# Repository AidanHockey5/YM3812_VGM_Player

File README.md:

# YM3812_VGM_Player
A Video Game Music player based on the YM3812 (OPL2) and Teensy 3.5.

You can view this project in action here:
https://www.youtube.com/watch?v=aLaUDFnNqQc

# Information about the main sound chips and VGM

The YM3812, AKA OPL2 was a staple FM soundchip of the early 1990's. It claim to fame was its inclusion on the Adlib and Soundblaster soundcards. OPL2 is THE FM sound of 1990's PC gaming.

VGM stands for Video Game Music, and it is a 44.1KHz logging format that stores real soundchip register information. My player will parse these files and send the data to the appropriate chips. You can learn more about the VGM file format here: http://www.smspower.org/Music/VGMFileFormat

http://www.smspower.org/uploads/Music/vgmspec170.txt?sid=58da937e68300c059412b536d4db2ca0

# Hook-up Guide

Teensy 3.5 | YM
------------ | -------------
23, 22, 21...17, 16 | D0-D7
34  | CS
33 | RD
32 | WR
31 | A0
30 | IC
29 | IRQ

The YM3812 requires a 3.579545 MHz signal to function properly. I just used a full-can crystal for this, but any clock source of that speed will work.
You will also need a Y3014B DAC IC along with an OP-amp (LM358).

# SD Card Information
The Teensy 3.5 has a built-in, high speed micro-SD card reader. You must format your SD card to Fat32 in order for this device to work correctly. Your SD card must only contain uncompressed .vgm files. VGZ FILES WILL NOT WORK! You may download .vgz files and use [7zip](http://www.7-zip.org/download.html) to extract the uncompressed file out of them. Vgm files on the SD card do not need to have the .vgm extension. As long as they contain valid, uncompressed vgm data, they will be read by the program regardless of their name.
You can find VGM files by Googling "myGameName VGM," or by checking out sites like http://vgmrips.net/packs/

# Control Over Serial
You can use a serial connection to control playback features. The commands are as follows:

Command | Result
------------ | -------------
\+ | Next Track
\- | Previous Track
\* | Random Track
\/ | Toggle Shuffle Mode
\. | Toggle Song Looping
r: | Request song

A song request is formatted as follows: ```r:mySongFile.vgm```
Once a song request is sent through the serial console, an attempt will be made to open that song file. The file must exist on the Teensy's SD card, and spelling/capitalization must be correct.
Need an easy-to-use serial console? [I've made one here.](https://github.com/AidanHockey5/OpenArduinoSerialConsole)

# Schematic

[PDF](https://github.com/AidanHockey5/YM3812_VGM_Player/raw/master/Schematics/OPL2_VGM_Player.pdf)

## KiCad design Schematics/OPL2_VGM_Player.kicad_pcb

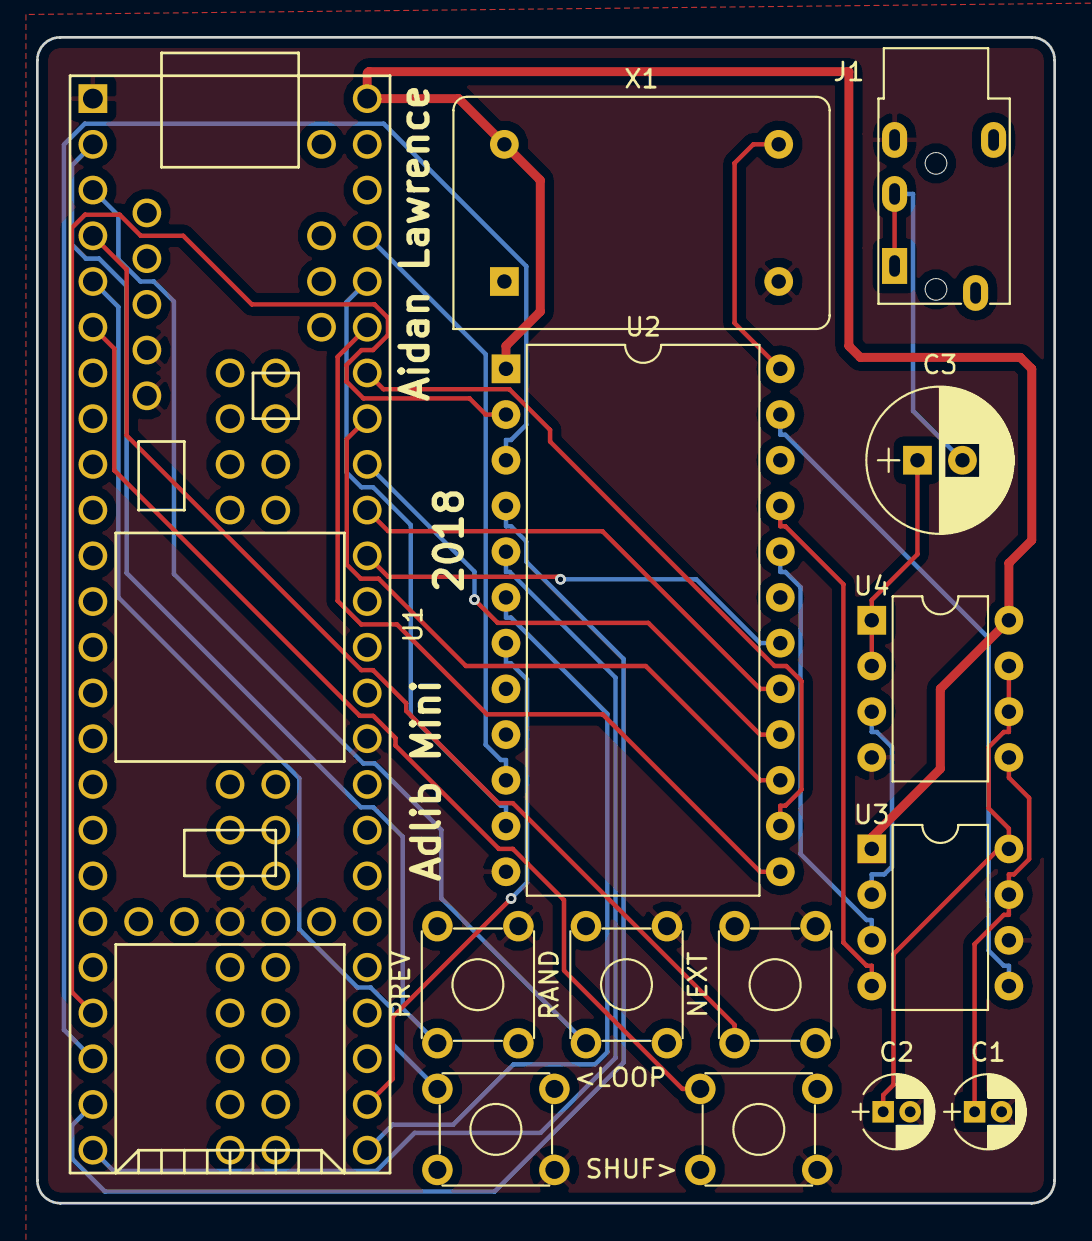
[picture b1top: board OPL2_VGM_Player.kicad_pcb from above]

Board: 2 copper layers, 56.5 x 64.8 mm, 14 parts (0 on the bottom side), 30 nets.

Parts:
<LOOP: LOOP; SW_TH_Tactile_Omron_B3F-10xx
C1, C2: 10uF; CP_Radial_D4.0mm_P1.50mm
C3: 1000uF; CP_Radial_D8.0mm_P2.50mm
J1: JACK_TRS_6PINS; PJ320E_3.5mm_Jack
NEXT: NEXT; SW_TH_Tactile_Omron_B3F-10xx
PREV: PREV; SW_TH_Tactile_Omron_B3F-10xx
RAND: RAND; SW_TH_Tactile_Omron_B3F-10xx
SHUF>: SHUF; SW_TH_Tactile_Omron_B3F-10xx
U1: Teensy3.5; Teensy35_36
U2: YM3812; DIP-24_W15.24mm
U3: Y3014B; DIP-8_W7.62mm
U4: LM358N; DIP-8_W7.62mm
X1: 3.579545MHz; Oscillator_DIP-14

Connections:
+5V: U1.53, U2.1, U3.1, U4.8, X1.14
BUF: U3.2, U4.3
D0: U1.50, U2.10
D1: U1.49, U2.11
D2: U1.48, U2.13
D3: U1.47, U2.14
D4: U1.46, U2.15
D5: U1.45, U2.16
D6: U1.44, U2.17
D7: U1.43, U2.18
GND: <LOOP.4, C1.2, C2.2, J1.3, NEXT.4, PREV.4, RAND.4, SHUF>.4, U1.1, U1.27, U1.39, U1.61, U1.62, U2.12, U3.6, U4.4, X1.7
LOOP: <LOOP.1, U1.5
NEXT: NEXT.1, U1.4
unnamed: C1.1, U3.7, U4.5
unnamed: C2.1, U3.8, U4.6, U4.7
unnamed: C3.1, U4.1, U4.2
unnamed: C3.2, J1.1, J1.2
unnamed: U2.20, U3.3
unnamed: U2.21, U3.4
unnamed: U2.23, U3.5
unnamed: U2.24, X1.8
PREV: PREV.1, U1.2
RAND: RAND.1, U1.3
SHUF: SHUF>.1, U1.6
YM_A0: U1.23, U2.4
YM_CS: U1.31, U2.7
YM_IC: U1.22, U2.3
YM_IRQ: U1.21, U2.2
YM_RD: U1.30, U2.6
YM_WR: U1.24, U2.5

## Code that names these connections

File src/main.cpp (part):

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
int YM_Datapins[8] = {23, 22, 21, 20, 19, 18, 17, 16};

const int YM_CS = 34;
const int YM_RD = 33;
const int YM_WR = 32;
const int YM_A0 = 31;
const int YM_IC = 30; 
const int YM_IRQ = 29;

YM3812 ym3812(YM_Datapins, YM_CS, YM_RD, YM_WR, YM_A0, YM_IRQ, YM_IC);

const int prev_btn = 0;
const int rand_btn = 1;
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
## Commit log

2018-01-18 Init. Everything all set up and working nicely!
2018-01-19 Fixed typos and reduced song startup delay
2018-01-21 Added schematics
2018-01-21 Added schematic image
2018-01-22 Updated schematics and PCB to support playback buttons.
2018-02-06 Fixed jack GND on board and schematic. Added control button support
2018-03-25 Update LICENSE
2018-03-31 Added local schematic symbols
2018-05-12 Fixed loop offset
